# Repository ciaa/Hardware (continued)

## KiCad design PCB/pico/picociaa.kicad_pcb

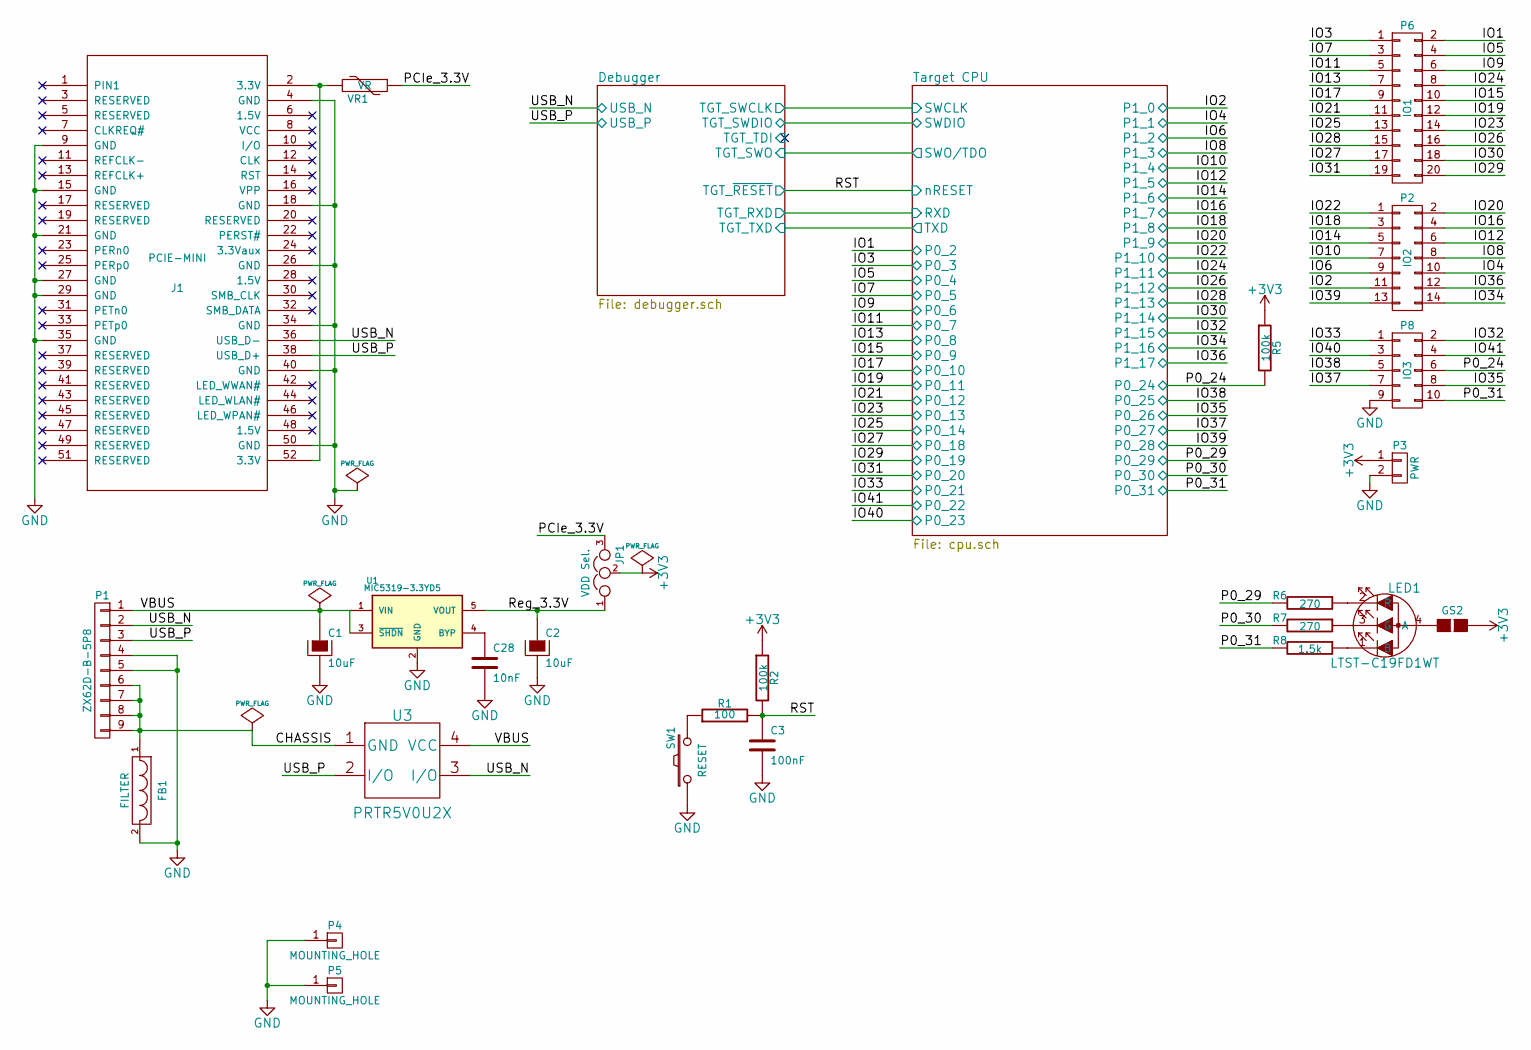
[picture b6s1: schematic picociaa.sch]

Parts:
C1, C2: 10uF; TantalC_SizeA_EIA-3216_Reflow
C3: 100nF; C_0603
C28: 10nF; C_0603
FB1: FILTER; R_0603
GS2: GS2
J1: PCIE-MINI; miniPCIeConn
JP1: VDD Sel.; Pin_Header_Straight_1x03_Pitch2.00mm
LED1: LTST-C19FD1WT; PLCC-4
P1: ZX62D-B-5P8; USB_microAB_ZX62-AB&B-5PA-11
P2: IO2; Pin_Header_Straight_2x07_Pitch2.00mm
P3: PWR; Pin_Header_Straight_1x02_Pitch2.00mm
P4, P5: MOUNTING_HOLE; PIN_ARRAY_1
P6: IO1; Pin_Header_Straight_2x10_Pitch2.00mm
P8: IO3; Pin_Header_Straight_2x05_Pitch2.00mm
R1: 100; R_0603
R2, R5: 100k; R_0603
R6, R7: 270; R_0603
R8: 1.5k; R_0603
SW1: RESET; SW_SPST_FSMSM
U1: MIC5319-3.3YD5; SOT-23-5
U3: PRTR5V0U2X; SOT-143
VR1: VR; R_1206

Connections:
+3V3: GS2.2 (G2), JP1.2, P3.1, R2.1, R5.1; also elsewhere on the board
/CHASSIS: FB1.1, P1.6, P1.7, P1.8, P1.9, U3.1 (GND)
/Debugger/TGT_~RESET~: C3.1, R1.2, R2.2; also elsewhere on the board
/Debugger/USB_N: J1.36 (USB_D-), P1.2, U3.3 (I/O); also elsewhere on the board
/Debugger/USB_P: J1.38 (USB_D+), P1.3, U3.2 (I/O); also elsewhere on the board
/PCIe_3.3V: JP1.3, VR1.1
/Reg_3.3V: C2.1, JP1.1, U1.5 (VOUT)
/Target CPU/P0_2: P6.2; also elsewhere on the board
/Target CPU/P0_3: P6.1; also elsewhere on the board
/Target CPU/P0_4: P6.4; also elsewhere on the board
/Target CPU/P0_5: P6.3; also elsewhere on the board
/Target CPU/P0_6: P6.6; also elsewhere on the board
/Target CPU/P0_7: P6.5; also elsewhere on the board
/Target CPU/P0_8: P6.7; also elsewhere on the board
/Target CPU/P0_9: P6.10; also elsewhere on the board
/Target CPU/P0_10: P6.9; also elsewhere on the board
/Target CPU/P0_11: P6.12; also elsewhere on the board
/Target CPU/P0_12: P6.11; also elsewhere on the board
/Target CPU/P0_13: P6.14; also elsewhere on the board
/Target CPU/P0_14: P6.13; also elsewhere on the board
/Target CPU/P0_18: P6.17; also elsewhere on the board
/Target CPU/P0_19: P6.20; also elsewhere on the board
/Target CPU/P0_20: P6.19; also elsewhere on the board
/Target CPU/P0_21: P8.1; also elsewhere on the board
/Target CPU/P0_22: P8.4; also elsewhere on the board
/Target CPU/P0_23: P8.3; also elsewhere on the board
/Target CPU/P0_24: P8.6, R5.2; also elsewhere on the board
/Target CPU/P0_25: P8.5; also elsewhere on the board
/Target CPU/P0_26: P8.8; also elsewhere on the board
/Target CPU/P0_27: P8.7; also elsewhere on the board
/Target CPU/P0_28: P2.13; also elsewhere on the board
/Target CPU/P0_29: R6.2; also elsewhere on the board
/Target CPU/P0_30: R7.2; also elsewhere on the board
/Target CPU/P0_31: P8.10, R8.2; also elsewhere on the board
/Target CPU/P1_0: P2.11; also elsewhere on the board
/Target CPU/P1_1: P2.10; also elsewhere on the board
/Target CPU/P1_2: P2.9; also elsewhere on the board
/Target CPU/P1_3: P2.8; also elsewhere on the board
/Target CPU/P1_4: P2.7; also elsewhere on the board
/Target CPU/P1_5: P2.6; also elsewhere on the board
/Target CPU/P1_6: P2.5; also elsewhere on the board
/Target CPU/P1_7: P2.4; also elsewhere on the board
/Target CPU/P1_8: P2.3; also elsewhere on the board
/Target CPU/P1_9: P2.2; also elsewhere on the board
/Target CPU/P1_10: P2.1; also elsewhere on the board
/Target CPU/P1_11: P6.8; also elsewhere on the board
/Target CPU/P1_12: P6.16; also elsewhere on the board
/Target CPU/P1_13: P6.15; also elsewhere on the board
/Target CPU/P1_14: P6.18; also elsewhere on the board
/Target CPU/P1_15: P8.2; also elsewhere on the board
/Target CPU/P1_16: P2.14; also elsewhere on the board
/Target CPU/P1_17: P2.12; also elsewhere on the board
/VBUS: C1.1, P1.1, U1.1 (VIN), U1.3 (~SHDN~), U3.4 (VCC)
GND: C1.2, C2.2, C3.2, C28.2, FB1.2, J1.4 (GND), J1.9 (GND), J1.15 (GND), J1.18 (GND), J1.21 (GND), J1.26 (GND), J1.27 (GND), J1.29 (GND), J1.34 (GND), J1.35 (GND), J1.40 (GND), J1.50 (GND), P1.4, P1.5, P3.2, P4.1, P5.1, P8.9, SW1.1, U1.2 (GND); also elsewhere on the board
unnamed: C28.1, U1.4 (BYP)
unnamed: GS2.1 (G1), LED1.4 (A)
unnamed: J1.2 (3.3V), J1.52 (3.3V), VR1.2
unnamed: LED1.1 (B), R8.1
unnamed: LED1.2 (R), R6.1
unnamed: LED1.3 (G), R7.1
unnamed: R1.1, SW1.2

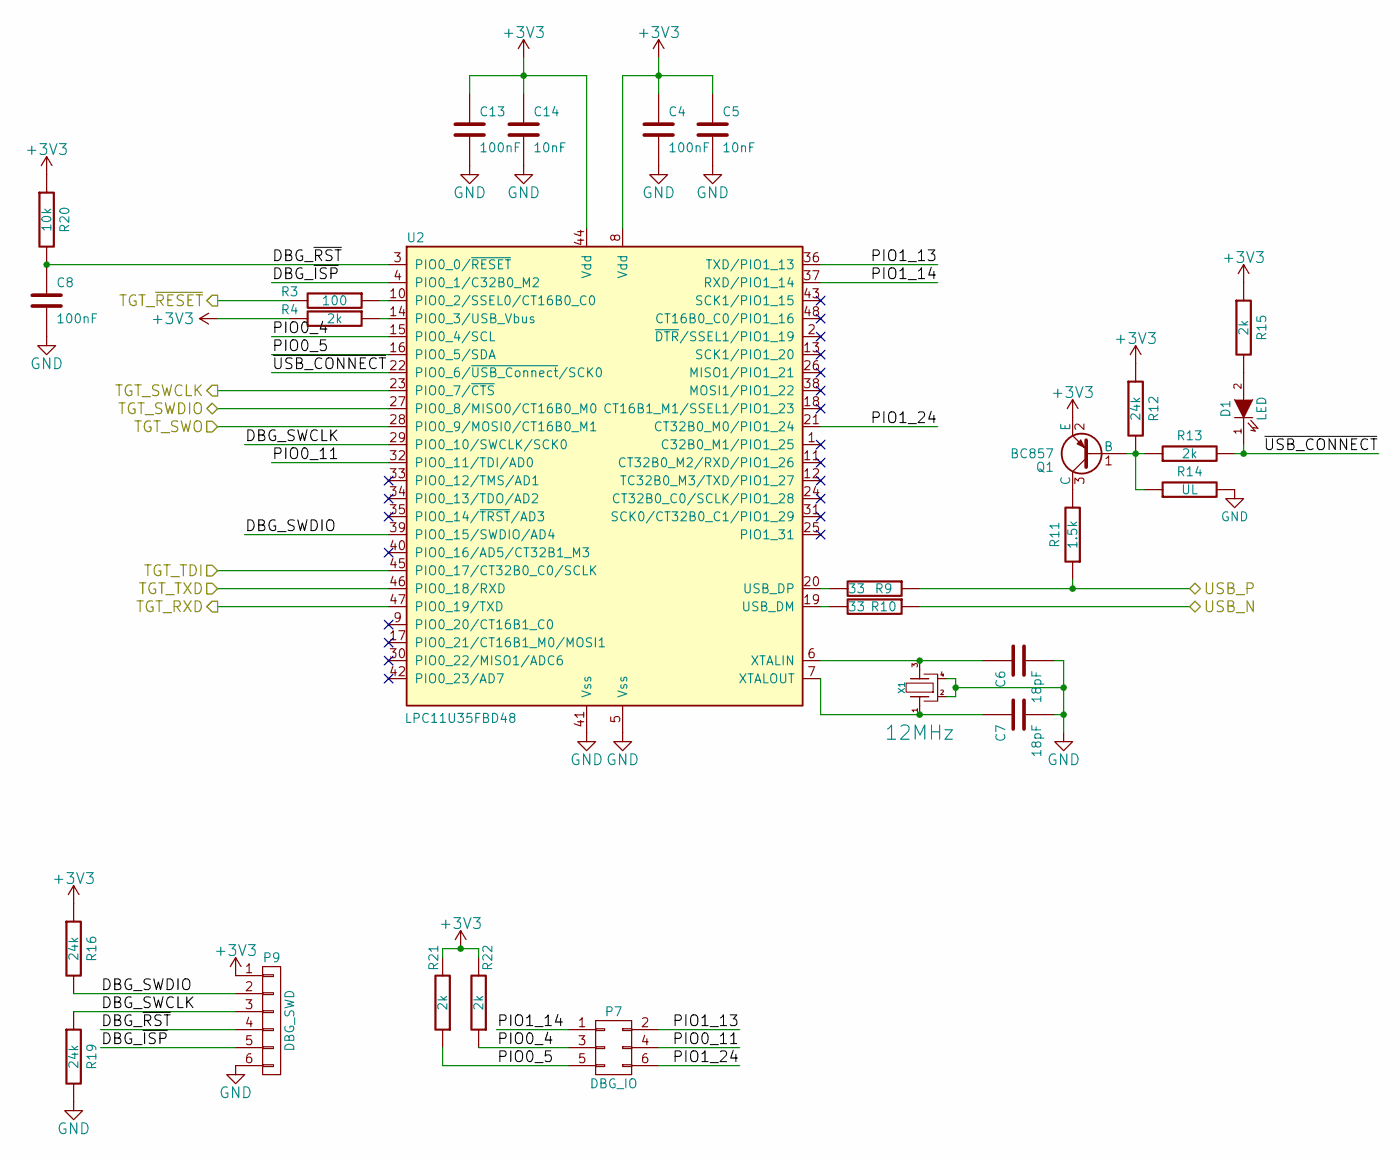
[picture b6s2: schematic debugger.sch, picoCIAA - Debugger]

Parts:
C4, C8, C13: 100nF; C_0603
C5, C14: 10nF; C_0603
C6, C7: 18pF; C_0603
D1: LED; LED_0603
P7: DBG_IO; Pin_Header_Straight_2x03_Pitch2.00mm
P9: DBG_SWD; Pin_Header_Straight_1x06_Pitch2.00mm
Q1: BC857; SOT-23
R3: 100; R_0603
R4, R13, R15, R21, R22: 2k; R_0603
R9, R10: 33; R_0603
R11: 1.5k; R_0603
R12, R16, R19: 24k; R_0603
R14: UL; R_0603
R20: 10k; R_0603
U2: LPC11U35FBD48; LQFP-48_7x7mm_Pitch0.5mm
X1: 12MHz; FA238V-XTAL; Digikey/Mouser 887-1831-1-ND

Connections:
+3V3: C4.1, C5.1, C13.1, C14.1, P9.1, Q1.2 (E), R4.2, R12.1, R15.1, R16.1, R20.1, R21.2, R22.2, U2.8 (Vdd), U2.44 (Vdd); also elsewhere on the board
/Debugger/DBG_SWCLK: P9.3, R19.1, U2.29 (PIO0_10/SWCLK/SCK0)
/Debugger/DBG_SWDIO: P9.2, R16.2, U2.39 (PIO0_15/SWDIO/AD4)
/Debugger/DBG_~ISP~: P9.5, U2.4 (PIO0_1/C32B0_M2)
/Debugger/DBG_~RST~: C8.1, P9.4, R20.2, U2.3 (PIO0_0/~RESET)
/Debugger/PIO0_4: P7.3, R22.1, U2.15 (PIO0_4/SCL)
/Debugger/PIO0_5: P7.5, R21.1, U2.16 (PIO0_5/SDA)
/Debugger/PIO0_11: P7.4, U2.32 (PIO0_11/TDI/AD0)
/Debugger/PIO1_13: P7.2, U2.36 (TXD/PIO1_13)
/Debugger/PIO1_14: P7.1, U2.37 (RXD/PIO1_14)
/Debugger/PIO1_24: P7.6, U2.21 (CT32B0_M0/PIO1_24)
/Debugger/TGT_TXD: U2.46 (PIO0_18/RXD); also elsewhere on the board
/Debugger/TGT_~RESET~: R3.2; also elsewhere on the board
/Debugger/USB_N: R10.1; also elsewhere on the board
/Debugger/USB_P: R9.1, R11.1; also elsewhere on the board
/Debugger/~USB_CONNECT~: D1.1 (K), R13.2, U2.22 (PIO0_6/~USB_Connect~/SCK0)
/Target CPU/RXD: U2.47 (PIO0_19/TXD); also elsewhere on the board
/Target CPU/SWCLK: U2.23 (PIO0_7/~CTS); also elsewhere on the board
/Target CPU/SWDIO: U2.27 (PIO0_8/MISO0/CT16B0_M0); also elsewhere on the board
/Target CPU/SWO/TDO: U2.28 (PIO0_9/MOSI0/CT16B0_M1); also elsewhere on the board
GND: C4.2, C5.2, C6.2, C7.2, C8.2, C13.2, C14.2, P9.6, R14.2, R19.2, U2.5 (Vss), U2.41 (Vss), X1.2 (GND), X1.4 (GND); also elsewhere on the board
unnamed: C6.1, U2.6 (XTALIN), X1.3 (B)
unnamed: C7.1, U2.7 (XTALOUT), X1.1 (A)
unnamed: D1.2 (A), R15.2
unnamed: Q1.1 (B), R12.2, R13.1, R14.1
unnamed: Q1.3 (C), R11.2
unnamed: R3.1, U2.10 (PIO0_2/SSEL0/CT16B0_C0)
unnamed: R4.1, U2.14 (PIO0_3/USB_Vbus)
unnamed: R9.2, U2.20 (USB_DP)
unnamed: R10.2, U2.19 (USB_DM)

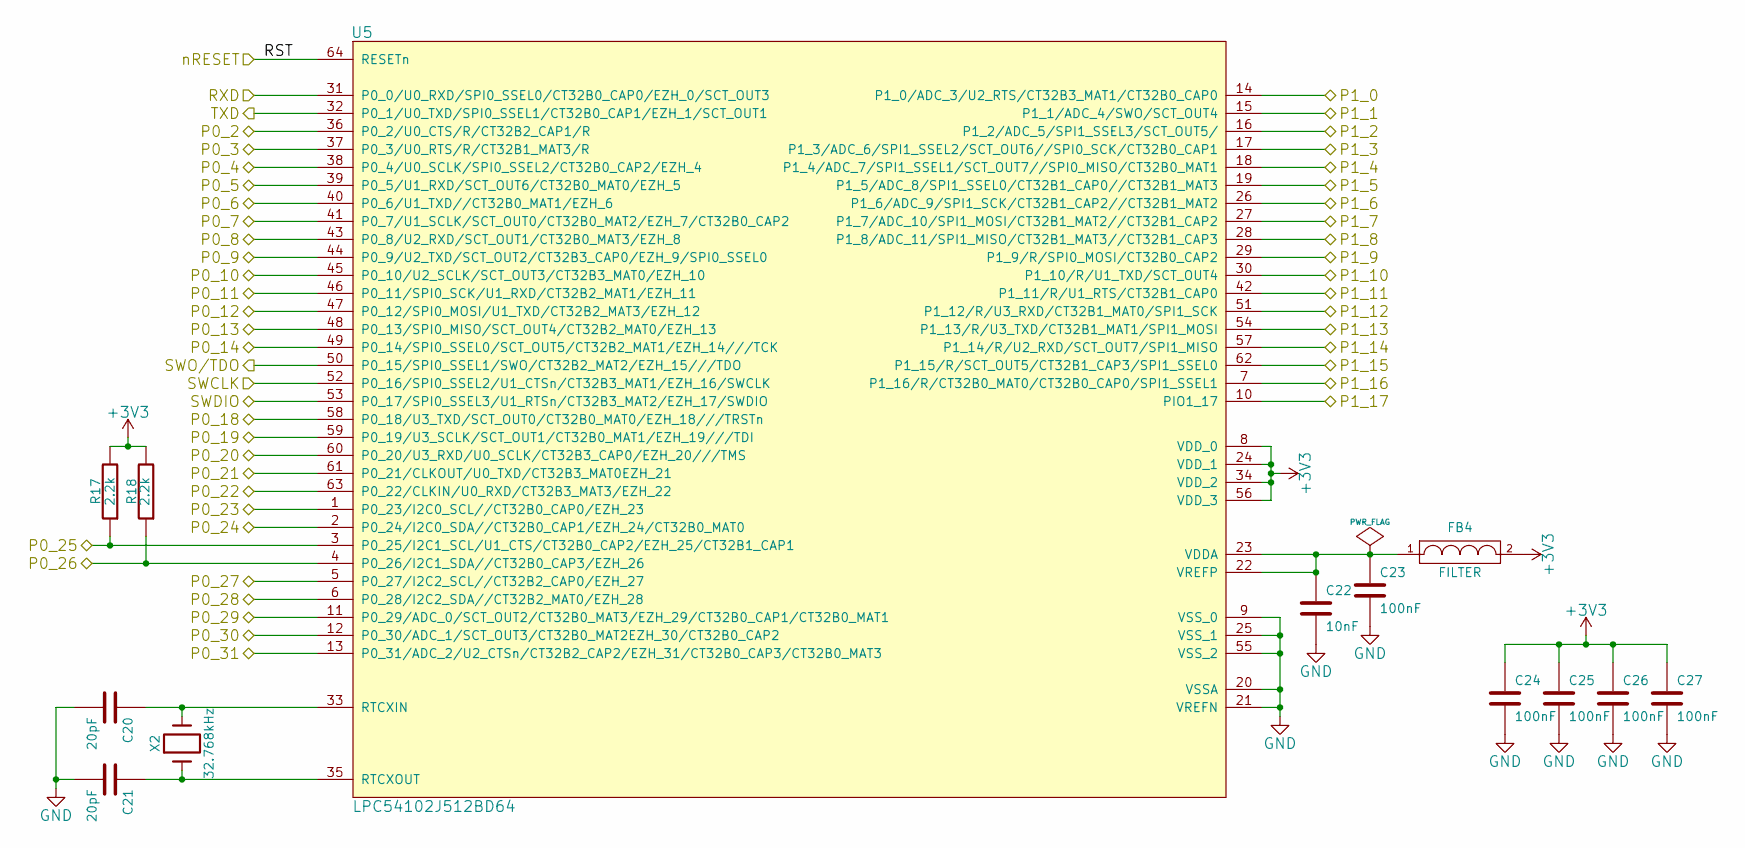
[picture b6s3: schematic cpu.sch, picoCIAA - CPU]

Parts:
C20, C21: 20pF; C_0603
C22: 10nF; C_0603
C23, C24, C25, C26, C27: 100nF; C_0603
FB4: FILTER; R_0603
R17, R18: 2.2k; R_0603
U5: LPC54102J512BD64; TQFP-64_10x10mm_Pitch0.5mm
X2: 32.768kHz; 4SOJ

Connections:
+3V3: C24.1, C25.1, C26.1, C27.1, FB4.2, R17.2, R18.2, U5.8 (VDD_0), U5.24 (VDD_1), U5.34 (VDD_2), U5.56 (VDD_3); also elsewhere on the board
/Debugger/TGT_TXD: U5.32 (P0_1/U0_TXD/SPI0_SSEL1/CT32B0_CAP1/EZH_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); also elsewhere on the board
/Debugger/TGT_~RESET~: U5.64 (RESETn); also elsewhere on the board
/Target CPU/P0_2: U5.36 (P0_2/U0_CTS/R/CT32B2_CAP1/R); also elsewhere on the board
/Target CPU/P0_3: U5.37 (P0_3/U0_RTS/R/CT32B1_MAT3/R); also elsewhere on the board
/Target CPU/P0_4: U5.38 (P0_4/U0_SCLK/SPI0_SSEL2/CT32B0_CAP2/EZH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); also elsewhere on the board
/Target CPU/P0_5: U5.39 (P0_5/U1_RXD/SCT_OUT6/CT32B0_MAT0/EZH_5); also elsewhere on the board
/Target CPU/P0_6: U5.40 (P0_6/U1_TXD//CT32B0_MAT1/EZH_6); also elsewhere on the board
/Target CPU/P0_7: U5.41 (P0_7/U1_SCLK/SCT_OUT0/CT32B0_MAT2/EZH_7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); also elsewhere on the board
/Target CPU/P0_8: U5.43 (P0_8/U2_RXD/SCT_OUT1/CT32B0_MAT3/EZH_8); also elsewhere on the board
/Target CPU/P0_9: U5.44 (P0_9/U2_TXD/SCT_OUT2/CT32B3_CAP0/EZH_9/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); also elsewhere on the board
/Target CPU/P0_10: U5.45 (P0_10/U2_SCLK/SCT_OUT3/CT32B3_MAT0/EZH_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); also elsewhere on the board
/Target CPU/P0_11: U5.46 (P0_11/SPI0_SCK/U1_RXD/CT32B2_MAT1/EZH_11); also elsewhere on the board
/Target CPU/P0_12: U5.47 (P0_12/SPI0_MOSI/U1_TXD/CT32B2_MAT3/EZH_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); also elsewhere on the board
/Target CPU/P0_13: U5.48 (P0_13/SPI0_MISO/SCT_OUT4/CT32B2_MAT0/EZ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); also elsewhere on the board
/Target CPU/P0_14: U5.49 (P0_14/SPI0_SSEL0/SCT_OUT5/CT32B2_MAT1/E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); also elsewhere on the board
/Target CPU/P0_18: U5.58 (P0_18/U3_TXD/SCT_OUT0/CT32B0_MAT0/EZH_1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); also elsewhere on the board
/Target CPU/P0_19: U5.59 (P0_19/U3_SCLK/SCT_OUT1/CT32B0_MAT1/EZH_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); also elsewhere on the board
/Target CPU/P0_20: U5.60 (P0_20/U3_RXD/U0_SCLK/CT32B3_CAP0/EZH_20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); also elsewhere on the board
/Target CPU/P0_21: U5.61 (P0_21/CLKOUT/U0_TXD/CT32B3_MAT0EZH_21); also elsewhere on the board
/Target CPU/P0_22: U5.63 (P0_22/CLKIN/U0_RXD/CT32B3_MAT3/EZH_22); also elsewhere on the board
/Target CPU/P0_23: U5.1 (P0_23/I2C0_SCL//CT32B0_CAP0/EZH_23); also elsewhere on the board
/Target CPU/P0_24: U5.2 (P0_24/I2C0_SDA//CT32B0_CAP1/EZH_24/CT32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); also elsewhere on the board
/Target CPU/P0_25: R17.1, U5.3 (P0_25/I2C1_SCL/U1_CTS/CT32B0_CAP2/EZH_2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); also elsewhere on the board
/Target CPU/P0_26: R18.1, U5.4 (P0_26/I2C1_SDA//CT32B0_CAP3/EZH_26); also elsewhere on the board
/Target CPU/P0_27: U5.5 (P0_27/I2C2_SCL//CT32B2_CAP0/EZH_27); also elsewhere on the board
/Target CPU/P0_28: U5.6 (P0_28/I2C2_SDA//CT32B2_MAT0/EZH_28); also elsewhere on the board
/Target CPU/P0_29: U5.11 (P0_29/ADC_0/SCT_OUT2/CT32B0_MAT3/EZH_29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); also elsewhere on the board
/Target CPU/P0_30: U5.12 (P0_30/ADC_1/SCT_OUT3/CT32B0_MAT2EZH_30/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); also elsewhere on the board
/Target CPU/P0_31: U5.13 (P0_31/ADC_2/U2_CTSn/CT32B2_CAP2/EZH_31/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); also elsewhere on the board
/Target CPU/P1_0: U5.14 (P1_0/ADC_3/U2_RTS/CT32B3_MAT1/CT32B0_CA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); also elsewhere on the board
/Target CPU/P1_1: U5.15 (P1_1/ADC_4/SWO/SCT_OUT4); also elsewhere on the board
/Target CPU/P1_2: U5.16 (P1_2/ADC_5/SPI1_SSEL3/SCT_OUT5/); also elsewhere on the board
/Target CPU/P1_3: U5.17 (P1_3/ADC_6/SPI1_SSEL2/SCT_OUT6//SPI0_SC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); also elsewhere on the board
/Target CPU/P1_4: U5.18 (P1_4/ADC_7/SPI1_SSEL1/SCT_OUT7//SPI0_MI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); also elsewhere on the board
/Target CPU/P1_5: U5.19 (P1_5/ADC_8/SPI1_SSEL0/CT32B1_CAP0//CT32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); also elsewhere on the board
/Target CPU/P1_6: U5.26 (P1_6/ADC_9/SPI1_SCK/CT32B1_CAP2//CT32B1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); also elsewhere on the board
/Target CPU/P1_7: U5.27 (P1_7/ADC_10/SPI1_MOSI/CT32B1_MAT2//CT32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); also elsewhere on the board
/Target CPU/P1_8: U5.28 (P1_8/ADC_11/SPI1_MISO/CT32B1_MAT3//CT32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); also elsewhere on the board
/Target CPU/P1_9: U5.29 (P1_9/R/SPI0_MOSI/CT32B0_CAP2); also elsewhere on the board
/Target CPU/P1_10: U5.30 (P1_10/R/U1_TXD/SCT_OUT4); also elsewhere on the board
/Target CPU/P1_11: U5.42 (P1_11/R/U1_RTS/CT32B1_CAP0); also elsewhere on the board
/Target CPU/P1_12: U5.51 (P1_12/R/U3_RXD/CT32B1_MAT0/SPI1_SCK); also elsewhere on the board
/Target CPU/P1_13: U5.54 (P1_13/R/U3_TXD/CT32B1_MAT1/SPI1_MOSI); also elsewhere on the board
/Target CPU/P1_14: U5.57 (P1_14/R/U2_RXD/SCT_OUT7/SPI1_MISO); also elsewhere on the board
/Target CPU/P1_15: U5.62 (P1_15/R/SCT_OUT5/CT32B1_CAP3/SPI1_SSEL0); also elsewhere on the board
/Target CPU/P1_16: U5.7 (P1_16/R/CT32B0_MAT0/CT32B0_CAP0/SPI1_SS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); also elsewhere on the board
/Target CPU/P1_17: U5.10 (PIO1_17); also elsewhere on the board
/Target CPU/RXD: U5.31 (P0_0/U0_RXD/SPI0_SSEL0/CT32B0_CAP0/EZH_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); also elsewhere on the board
/Target CPU/SWCLK: U5.52 (P0_16/SPI0_SSEL2/U1_CTSn/CT32B3_MAT1/EZ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); also elsewhere on the board
/Target CPU/SWDIO: U5.53 (P0_17/SPI0_SSEL3/U1_RTSn/CT32B3_MAT2/EZ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); also elsewhere on the board
/Target CPU/SWO/TDO: U5.50 (P0_15/SPI0_SSEL1/SWO/CT32B2_MAT2/EZH_15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); also elsewhere on the board
GND: C20.2, C21.2, C22.2, C23.2, C24.2, C25.2, C26.2, C27.2, U5.9 (VSS_0), U5.20 (VSSA), U5.21 (VREFN), U5.25 (VSS_1), U5.55 (VSS_2); also elsewhere on the board
unnamed: C20.1, U5.33 (RTCXIN), X2.2
unnamed: C21.1, U5.35 (RTCXOUT), X2.1
unnamed: C22.1, C23.1, FB4.1, U5.22 (VREFP), U5.23 (VDDA)

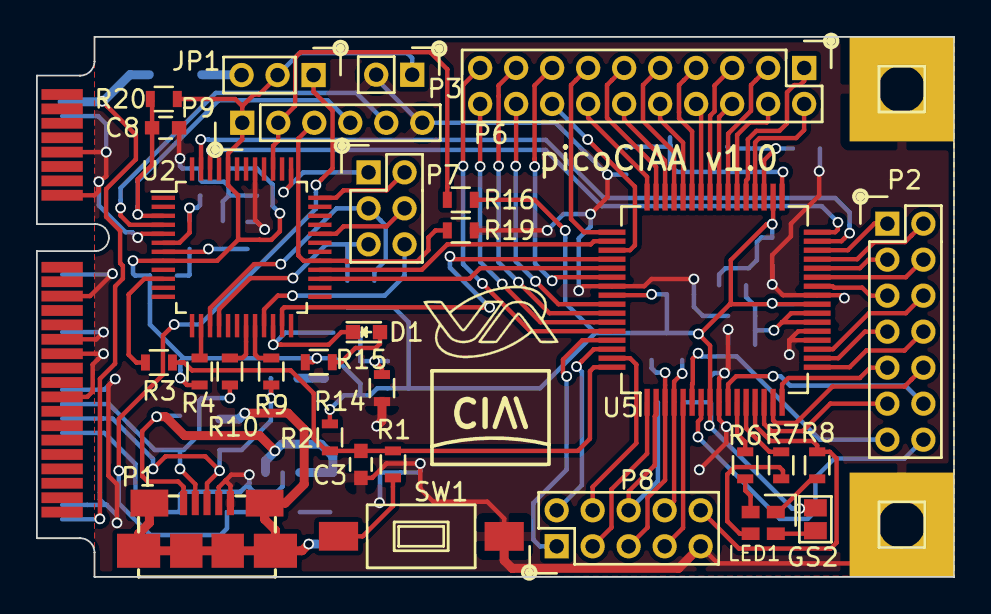
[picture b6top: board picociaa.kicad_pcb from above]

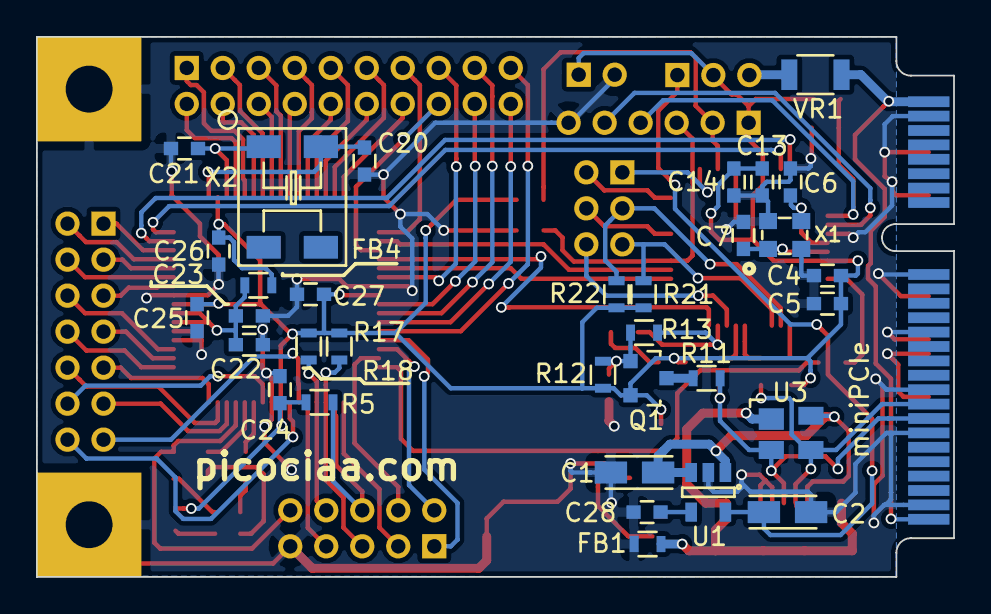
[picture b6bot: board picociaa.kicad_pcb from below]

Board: 2 copper layers, 51.0 x 30.0 mm, 66 parts (33 on the bottom side), 89 nets.

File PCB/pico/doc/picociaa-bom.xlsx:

Item | Qty | Reference(s) | Value | Link Mouser | Nro. Parte
1 | 2 | C1, C2 | 10uF | T491A106K010AT | T491A106K010AT
2 | 9 | C13, C23, C24, C25, C26, C27, C3, C4, C8 | 100nF | 80-C0603C104K5R | 80-C0603C104K5R
3 | 4 | C14, C22, C28, C5 | 10nF | 80-C0603C103K5R | 80-C0603C103K5R
4 | 2 | C20, C21 | 20pF | 81-GRM39C200J50 | 81-GRM39C200J50
5 | 2 | C6, C7 | 18pF | 81-GRM39C180J50 | 81-GRM39C180J50
6 | 1 | D1 | LED | 78-VLMS1300-GS08 | 78-VLMS1300-GS08
7 | 2 | FB1, FB4 | FILTER | 810-MMZ1608B601C | 810-MMZ1608B601C
8 | 1 | G1 | LOGO | 0
9 | 1 | GS2 | GS2 | 0
10 | 1 | J1 | PCIE-MINI | 0
11 | 1 | JP1 | VDD Sel. JUMPER | 855-M22-1920005 | 855-M22-1920005
 |  |  | VDD Sel. Pines | 855-M22-2510305 | 855-M22-2510305 | pines 2mm 1 fila
12 | 1 | LED1 | RGB | 859-LTST-C19FD1WT | 859-LTST-C19FD1WT
13 | 1 | P1 | MicroUSB tipo B | 649-10118192-0001LF | 649-10118192-0001LF |  | housings
14 | 1 | P2 | IO2 | 855-M22-2520705 | 855-M22-2520705 | pines 2mm 2 filas | 538-511101451
15 | 1 | P3 | PWR | 855-M22-2510205 | 855-M22-2510205 | pines 2mm 1 fila | 538-51090-0200
16 | 2 | P4, P5 | MOUNTING_HOLE | 0
17 | 1 | P6 | IO1 | 855-M22-2521005 | 855-M22-2521005 | pines 2mm 2 filas | 538-511102051
18 | 1 | P7 | DBG_IO | 855-M22-2520305 | 855-M22-2520305 | pines 2mm 2 filas | 538-51110-0660
19 | 1 | P8 | IO3 | 855-M22-2520505 | 855-M22-2520505 | pines 2mm 2 filas | 538-51110-1050
20 | 1 | P9 | DBG_SWD | 855-M22-2510605 | 855-M22-2510605 | pines 2mm 1 fila | 538-51090-0600
21 | 1 | Q1 | BC857 | 863-BC857BLT1G | 863-BC857BLT1G
22 | 2 | R1, R3 | 100 | 71-CRCW0603-100-E3 | 71-CRCW0603-100-E3
23 | 2 | R10, R9 | 33 | 71-CRCW0603-33-E3 | 71-CRCW0603-33-E3
24 | 2 | R11, R8 | 1.5k | 71-CRCW0603-1.5K-E3 | 71-CRCW0603-1.5K-E3
25 | 3 | R12, R16, R19 | 24k | 71-CRCW0603-24K-E3 | 71-CRCW0603-24K-E3
26 | 5 | R13, R15, R4, R21, R22 | 2k | 71-CRCW0603-2.0K-E3 | 71-CRCW0603-2.0K-E3
27 | 1 | R14 | UL | 0
28 | 2 | R17, R18 | 2.2k | 71-CRCW0603-2.2K-E3 | 71-CRCW0603-2.2K-E3
29 | 2 | R2, R5 | 100k | 71-CRCW0603-100K-E3 | 71-CRCW0603-100K-E3
30 | 1 | R20 | 10k | 71-CRCW0603-10K-E3 | 71-CRCW0603-10K-E3
31 | 2 | R6, R7 | 270 | 71-CRCW0603-270-E3 | 71-CRCW0603-270-E3
32 | 1 | SW1 | RESET | 506-FSMSM | 506-FSMSM
33 | 1 | U1 | MIC5319-3.3YD5 | 998-MIC5319-3.3YD5TR | 998-MIC5319-3.3YD5TR
34 | 1 | U2 | LPC11U35FBD48 | 771-LPC11U35FBD48401 | 771-LPC11U35FBD48401
35 | 1 | U3 | PRTR5V0U2X | 771-PRTR5V0U2X-T/R | 771-PRTR5V0U2X-T/R
36 | 1 | U5 | LPC54102J512BD64 | 771-LPC54102J512BD64 | 771-LPC54102J512BD64
37 | 1 | VR1 | VR | 504-PTS12066V100 | 504-PTS12066V100
38 | 1 | X1 | 12MHz | 581-CX2520DB1C0WLSC1 | 581-CX2520DB1C0WLSC1
39 | 1 | X2 | 32.768kHz | 815-ABS25-32.768KHZT | 815-ABS25-32.768KHZT
